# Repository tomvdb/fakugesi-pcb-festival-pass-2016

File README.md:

# fakugesi-pcb-festival-pass-2016
Design files for the fakugesi 2016 festival pass

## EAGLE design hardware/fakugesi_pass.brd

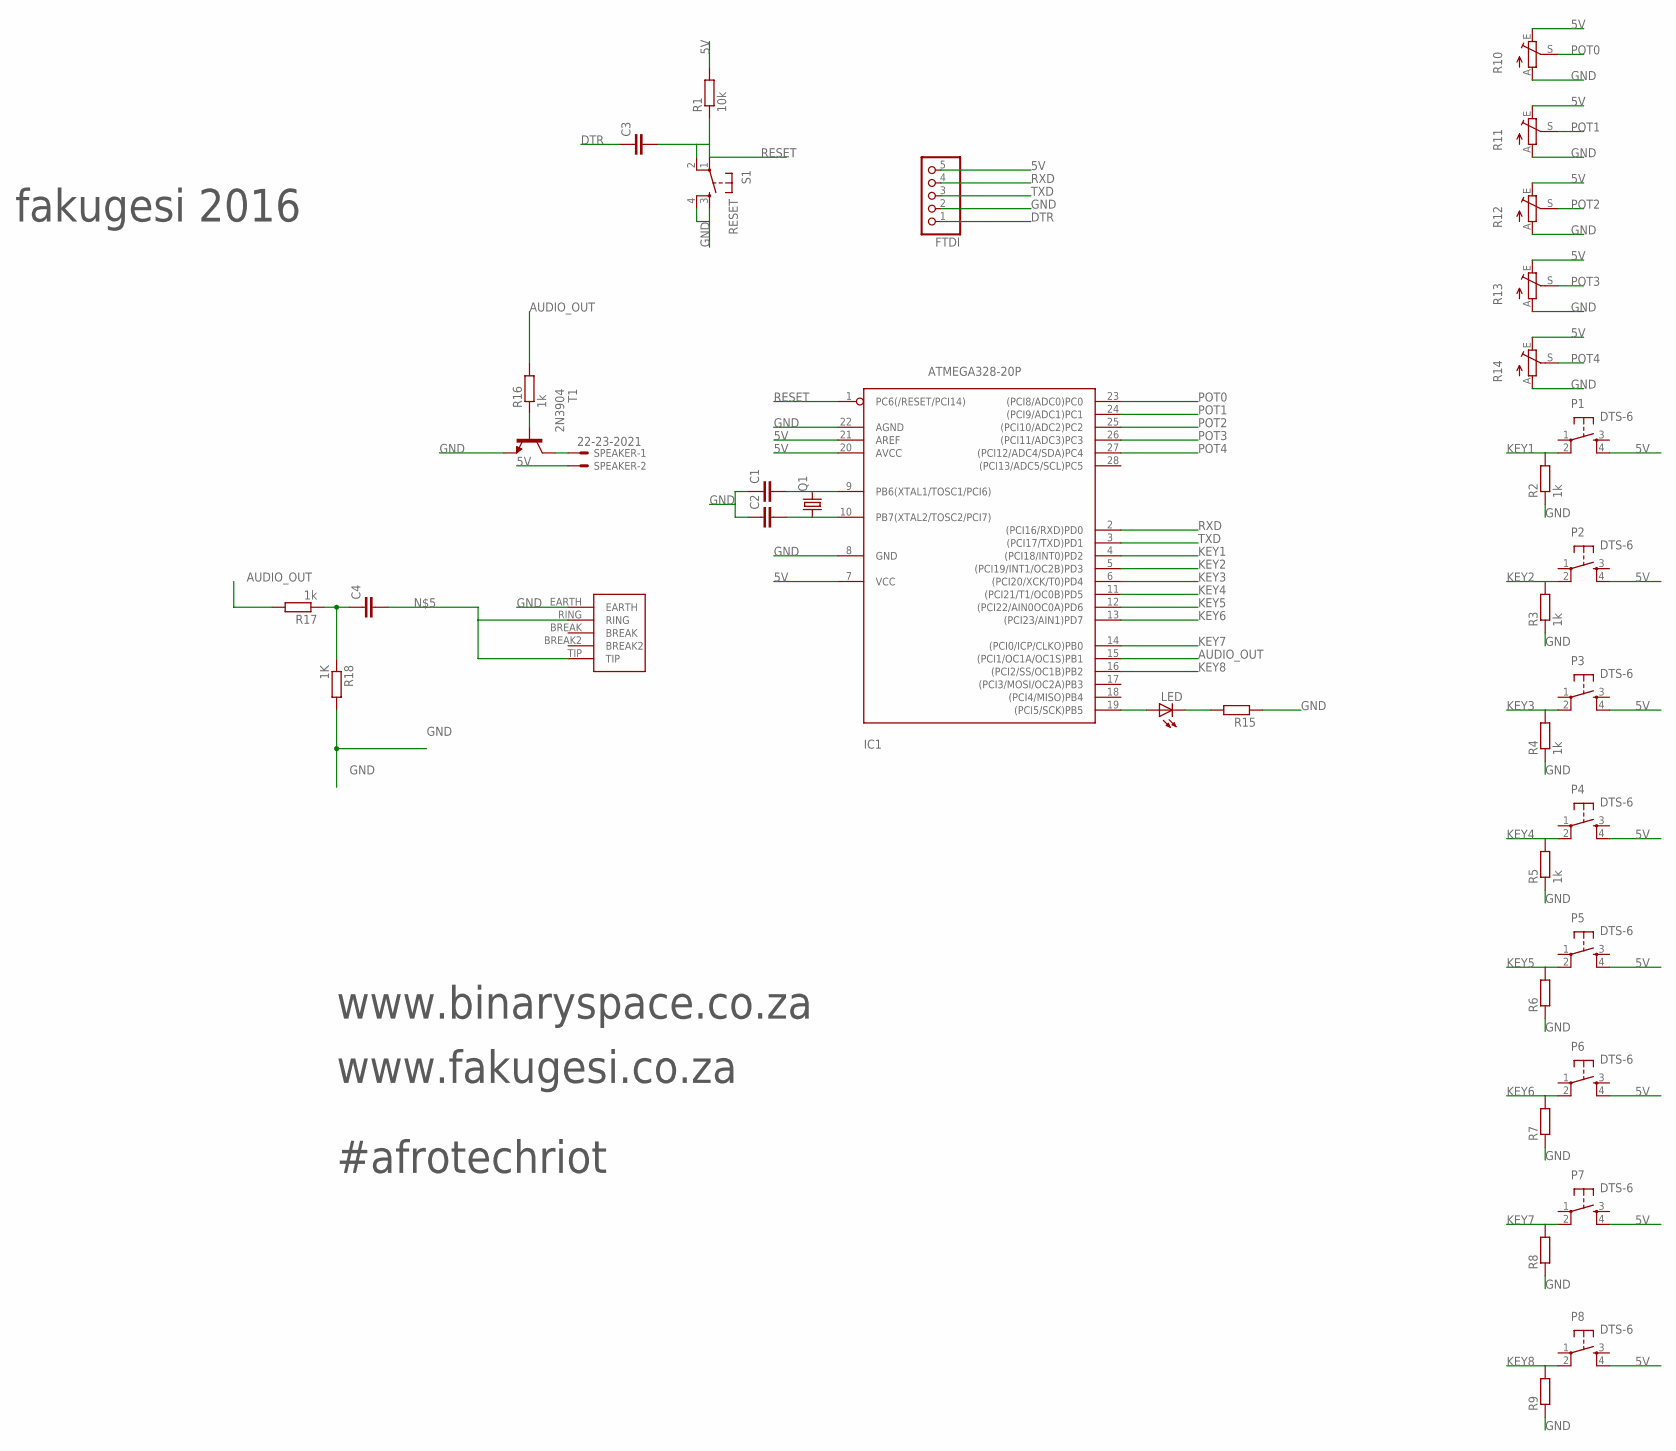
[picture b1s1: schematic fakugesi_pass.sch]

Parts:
C1, C2, C3, C4: C2.5/5; C2.5-5
FTDI: HEADER-1X5; 1X05_OVAL
IC1: ATMEGA328-20P; DIL28-3
LED: LED3MM
P1, P2, P3, P4, P5, P6, P7, P8: DTS-6
Q1: CRYTALHC49S; HC49/S
R1: 10k; 0207/7
R2, R3, R4, R5, R16, R17: 1k; 0207/7
R6, R7, R8, R9, R15: R-EU_0207/7; 0207/7
R10, R11, R12, R13, R14: TRIM_EU-RS3; RS3
R18: 1K; 0207/7
S1: RESET; DTS-6
SPEAKER: 22-23-2021
T1: 2N3904; TO92
U$1: 3.5MMAUDIOJACKPCB; 3.5MMAUDIOJACK

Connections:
5V: FTDI.5, IC1.7 (VCC), IC1.20 (AVCC), IC1.21 (AREF), P1.4, P2.4, P3.4, P4.4, P5.4, P6.4, P7.4, P8.4, R1.2, R10.E, R11.E, R12.E, R13.E, R14.E, SPEAKER.2
AUDIO_OUT: IC1.15 ((PCI1/OC1A/OC1S)PB1), R16.2, R17.2
DTR: C3.1, FTDI.1
GND: C1.1, C2.1, FTDI.2, IC1.8 (GND), IC1.22 (AGND), R2.1, R3.1, R4.1, R5.1, R6.1, R7.1, R8.1, R9.1, R10.A, R11.A, R12.A, R13.A, R14.A, R15.1, R18.2, S1.3, S1.4, T1.3 (E), U$1.EARTH
KEY1: IC1.4 ((PCI18/INT0)PD2), P1.2, R2.2
KEY2: IC1.5 ((PCI19/INT1/OC2B)PD3), P2.2, R3.2
KEY3: IC1.6 ((PCI20/XCK/T0)PD4), P3.2, R4.2
KEY4: IC1.11 ((PCI21/T1/OC0B)PD5), P4.2, R5.2
KEY5: IC1.12 ((PCI22/AIN0OC0A)PD6), P5.2, R6.2
KEY6: IC1.13 ((PCI23/AIN1)PD7), P6.2, R7.2
KEY7: IC1.14 ((PCI0/ICP/CLKO)PB0), P7.2, R8.2
KEY8: IC1.16 ((PCI2/SS/OC1B)PB2), P8.2, R9.2
unnamed: SPEAKER.1, T1.1 (C)
unnamed: C4.1, R17.1, R18.1
unnamed: IC1.19 ((PCI5/SCK)PB5), LED.A
unnamed: LED.K (C), R15.2
unnamed: C4.2, U$1.RING, U$1.TIP
unnamed: R16.1, T1.2 (B)
POT0: IC1.23 ((PCI8/ADC0)PC0), R10.S
POT1: IC1.24 ((PCI9/ADC1)PC1), R11.S
POT2: IC1.25 ((PCI10/ADC2)PC2), R12.S
POT3: IC1.26 ((PCI11/ADC3)PC3), R13.S
POT4: IC1.27 ((PCI12/ADC4/SDA)PC4), R14.S
RESET: C3.2, IC1.1 (PC6(/RESET/PCI14)), R1.1, S1.1, S1.2
RXD: FTDI.4, IC1.2 ((PCI16/RXD)PD0)
TXD: FTDI.3, IC1.3 ((PCI17/TXD)PD1)
XTAL1: C1.2, IC1.9 (PB6(XTAL1/TOSC1/PCI6)), Q1.2
XTAL2: C2.2, IC1.10 (PB7(XTAL2/TOSC2/PCI7)), Q1.1

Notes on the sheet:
www.binaryspace.co.za
www.fakugesi.co.za
#afrotechriot
fakugesi 2016

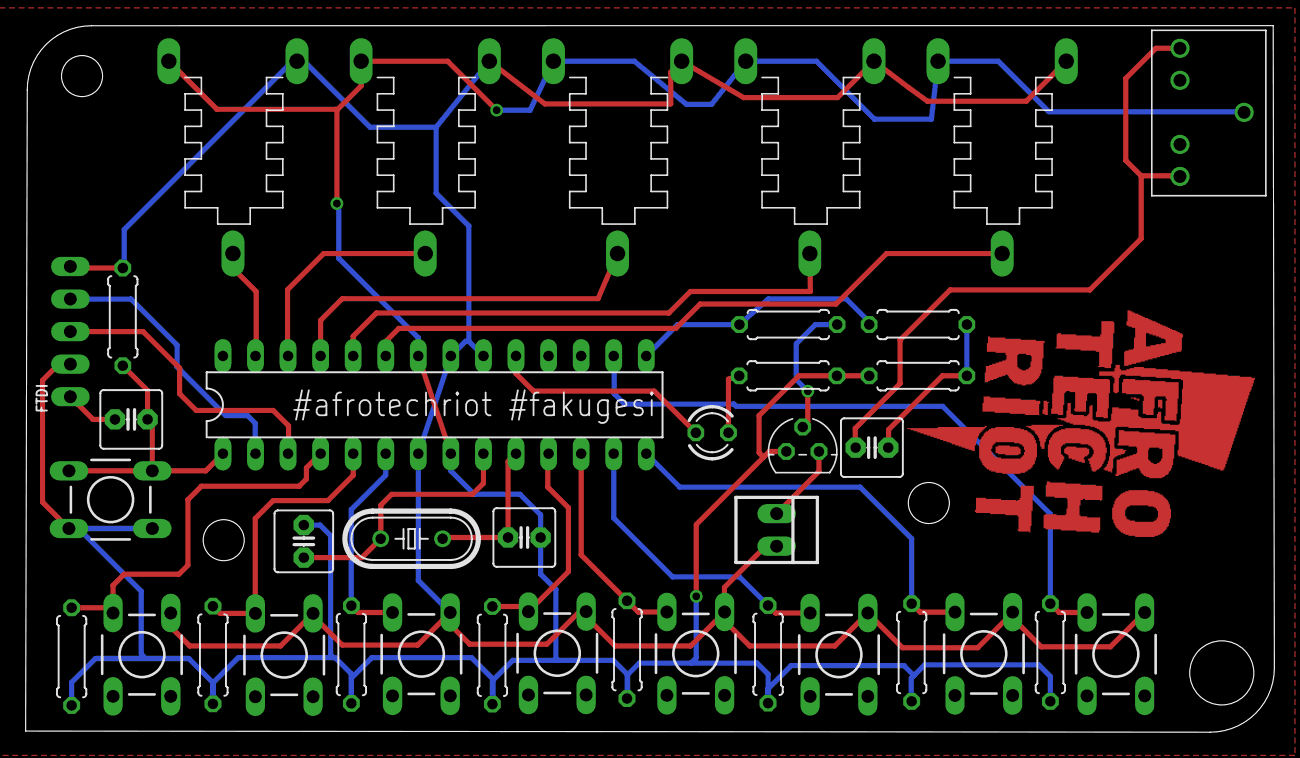
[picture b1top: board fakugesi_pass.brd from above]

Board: 2 copper layers, 97.4 x 55.1 mm, 38 parts (0 on the bottom side), 28 nets.

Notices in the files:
parts and their libraries:
microbuilder: This work is placed in the public domain, and may be freely used for commercial and non-commercial work with the following conditions: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
